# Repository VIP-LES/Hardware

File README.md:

# Hardware
Eagle files for custom PCBs used on launches

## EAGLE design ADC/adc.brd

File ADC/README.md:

ADC Breakout board for MCP3002 (MSOP packaging) and MCP601 (SOIC packaging). Vdd powers the MCP601 op amp, and Vref powers the MCP3002 ADC and provides the reference voltage. The maximum input voltage on pin IN is Vdd - 1.2V. Refer to the [MCP3002 datasheet](http://ww1.microchip.com/downloads/en/DeviceDoc/21294E.pdf) for SPI documentation.

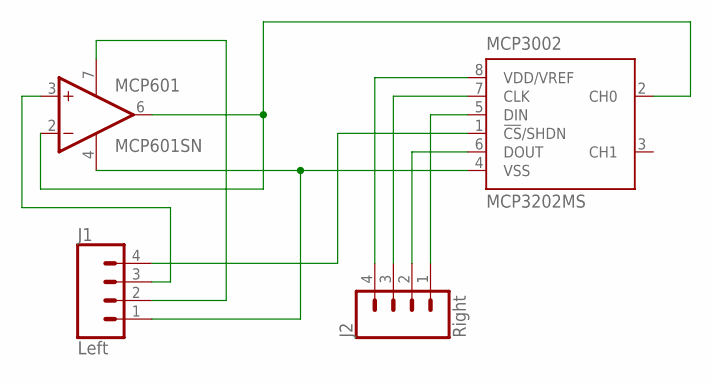
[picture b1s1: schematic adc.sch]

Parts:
J1: Left; 1X04
J2: Right; 1X04
MCP601: MCP601SN; SO08
MCP3002: MCP3202MS; MSOP8

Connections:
unnamed: MCP601.2 (-IN), MCP601.6 (OUT), MCP3002.2 (CH0)
unnamed: J1.3, MCP601.3 (+IN)
unnamed: J2.4, MCP3002.8 (VDD/VREF)
unnamed: J2.3, MCP3002.7 (CLK)
unnamed: J2.2, MCP3002.6 (DOUT)
unnamed: J2.1, MCP3002.5 (DIN)
unnamed: J1.4, MCP3002.1 (!CS!/SHDN)
V+: J1.2, MCP601.7 (V+)
V-: J1.1, MCP601.4 (V-), MCP3002.4 (VSS)

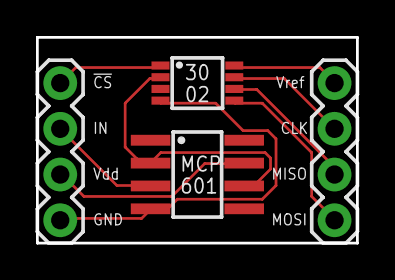
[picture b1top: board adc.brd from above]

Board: 2 copper layers, 17.8 x 11.4 mm, 4 parts (0 on the bottom side), 9 nets.

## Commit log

2017-11-02 Rename adc.brd to ADC/adc.brd
2017-11-02 Rename adc.sch to ADC/adc.sch
2017-11-04 Updated silkscreen
2017-11-12 Updated silkscreen
    Increased size of silkscreen text that was illegible on prototype PCB

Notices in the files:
parts and their libraries:
SparkFun-Connectors: Licensing: Creative Commons ShareAlike 4.0 International - https://creativecommons.org/licenses/by-sa/4.0
